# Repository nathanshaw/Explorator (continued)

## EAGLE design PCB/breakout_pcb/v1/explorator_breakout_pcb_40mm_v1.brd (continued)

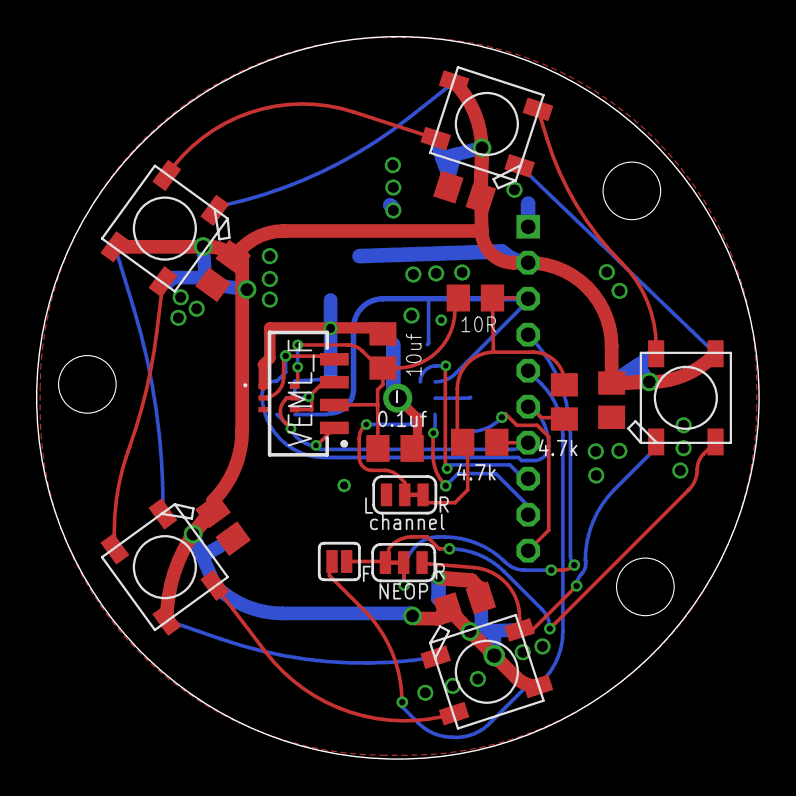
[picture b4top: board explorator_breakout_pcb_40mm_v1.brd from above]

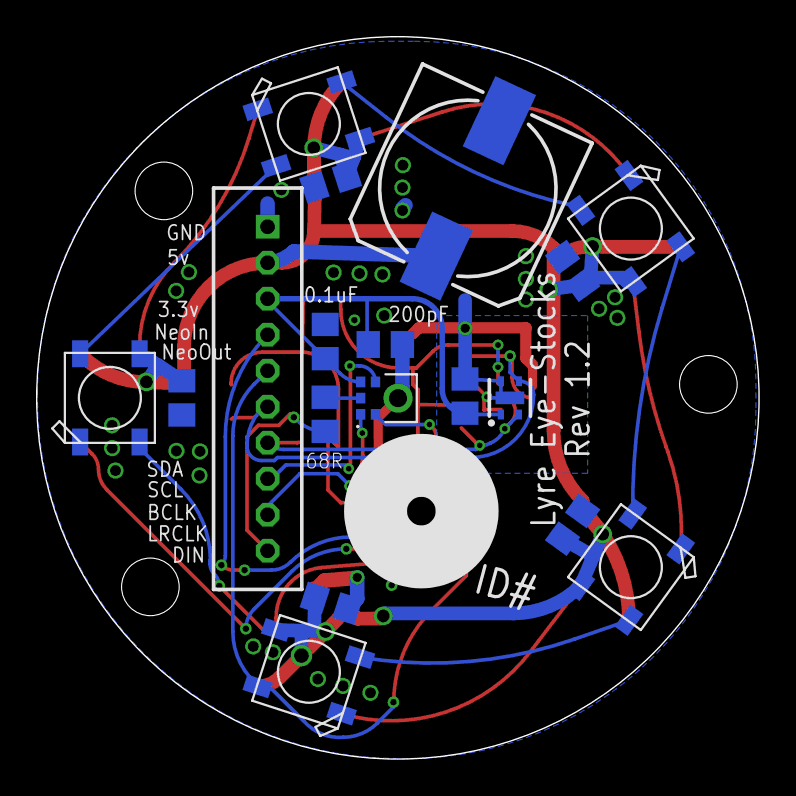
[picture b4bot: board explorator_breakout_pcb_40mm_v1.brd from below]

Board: 2 copper layers, 40.1 x 40.1 mm, 38 parts (18 on the bottom side), 23 nets.

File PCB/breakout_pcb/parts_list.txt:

Partlist

Exported from explorator_breakout_pcb_40mm_v2.sch at 3/21/23 11:15 AM

EAGLE Version 9.6.2 Copyright (c) 1988-2020 Autodesk, Inc.

Assembly variant: 

Part     Value                  Device                 Package                         Library              Sheet

C1       0.1uf                  C-USC0805              C0805                           rcl                  1
C2       0.1uF                  C-USC0805              C0805                           rcl                  1
C3       1mF                    CPOL-EU153CLV-1012     153CLV-1012                     rcl                  1
C4       10uf                   C-USC0805              C0805                           rcl                  1
C8       0.1uF                  C-USC0805              C0805                           rcl                  1
C9       200pF                  C-USC0805              C0805                           rcl                  1
JP1      JUMPER-SMT-3POS_NC_ONE JUMPER-SMT-3POS_NC_ONE SMT-JUMPER_3_1-NC_TRACE_NO-SILK nathans-custom-parts 1
JP3      JUMPER-SMT-3POS_NC_ONE JUMPER-SMT-3POS_NC_ONE SMT-JUMPER_3_1-NC_TRACE_NO-SILK nathans-custom-parts 1
JP4      JUMPER-SMT-2POS        JUMPER-SMT-2POS        SMT-JUMPER_2_NO_NO-SILK         nathans-custom-parts 1
MK_REAR  SPH-IMPROVED           SPH-IMPROVED           MIC_SPH0645LM4H-B_LARGER_RING   SPH0645LM4H-B        1
NC1      0.1uf                  C-USC0805              C0805                           rcl                  1
NC2      0.1uf                  C-USC0805              C0805                           rcl                  1
NC3      0.1uf                  C-USC0805              C0805                           rcl                  1
NC4      0.1uf                  C-USC0805              C0805                           rcl                  1
NC5      0.1uf                  C-USC0805              C0805                           rcl                  1
NC6      0.1uf                  C-USC0805              C0805                           rcl                  1
NC7      0.1uf                  C-USC0805              C0805                           rcl                  1
NC8      0.1uf                  C-USC0805              C0805                           rcl                  1
NC9      0.1uf                  C-USC0805              C0805                           rcl                  1
NC10     0.1uf                  C-USC0805              C0805                           rcl                  1
NEO_01   WS2812                 WS2812                 WS2812B                         WS2812B              1
NEO_02   WS2812                 WS2812                 WS2812B                         WS2812B              1
NEO_03   WS2812                 WS2812                 WS2812B                         WS2812B              1
NEO_04   WS2812                 WS2812                 WS2812B                         WS2812B              1
NEO_05   WS2812                 WS2812                 WS2812B                         WS2812B              1
NEO_06   WS2812                 WS2812                 WS2812B                         WS2812B              1
NEO_07   WS2812                 WS2812                 WS2812B                         WS2812B              1
NEO_08   WS2812                 WS2812                 WS2812B                         WS2812B              1
NEO_09   WS2812                 WS2812                 WS2812B                         WS2812B              1
NEO_10   WS2812                 WS2812                 WS2812B                         WS2812B              1
P1       B10B-PH-K              B10B-PH-K              B10B-PH-K                       con-jst-ph           1
R3       10R                    R-US_R0805             R0805                           PulseOximeterECG_AU  1
R5       4.7k                   R-US_R0805             R0805                           PulseOximeterECG_AU  1
R6       4.7k                   R-US_R0805             R0805                           PulseOximeterECG_AU  1
R15      68R                    R-US_R0805             R0805                           PulseOximeterECG_AU  1
U1       SHTC3                  SHTC3                  SHTC3                           SHTC3                1
U2       VEML6030-GS15          VEML6030-GS15          VISHAY_VEML6030_2X2X0.87        VEML6030-GS15        1
VEML_F   VEML7700-TT            VEML7700-TT            VEML7700                        VEML7700-TT          1

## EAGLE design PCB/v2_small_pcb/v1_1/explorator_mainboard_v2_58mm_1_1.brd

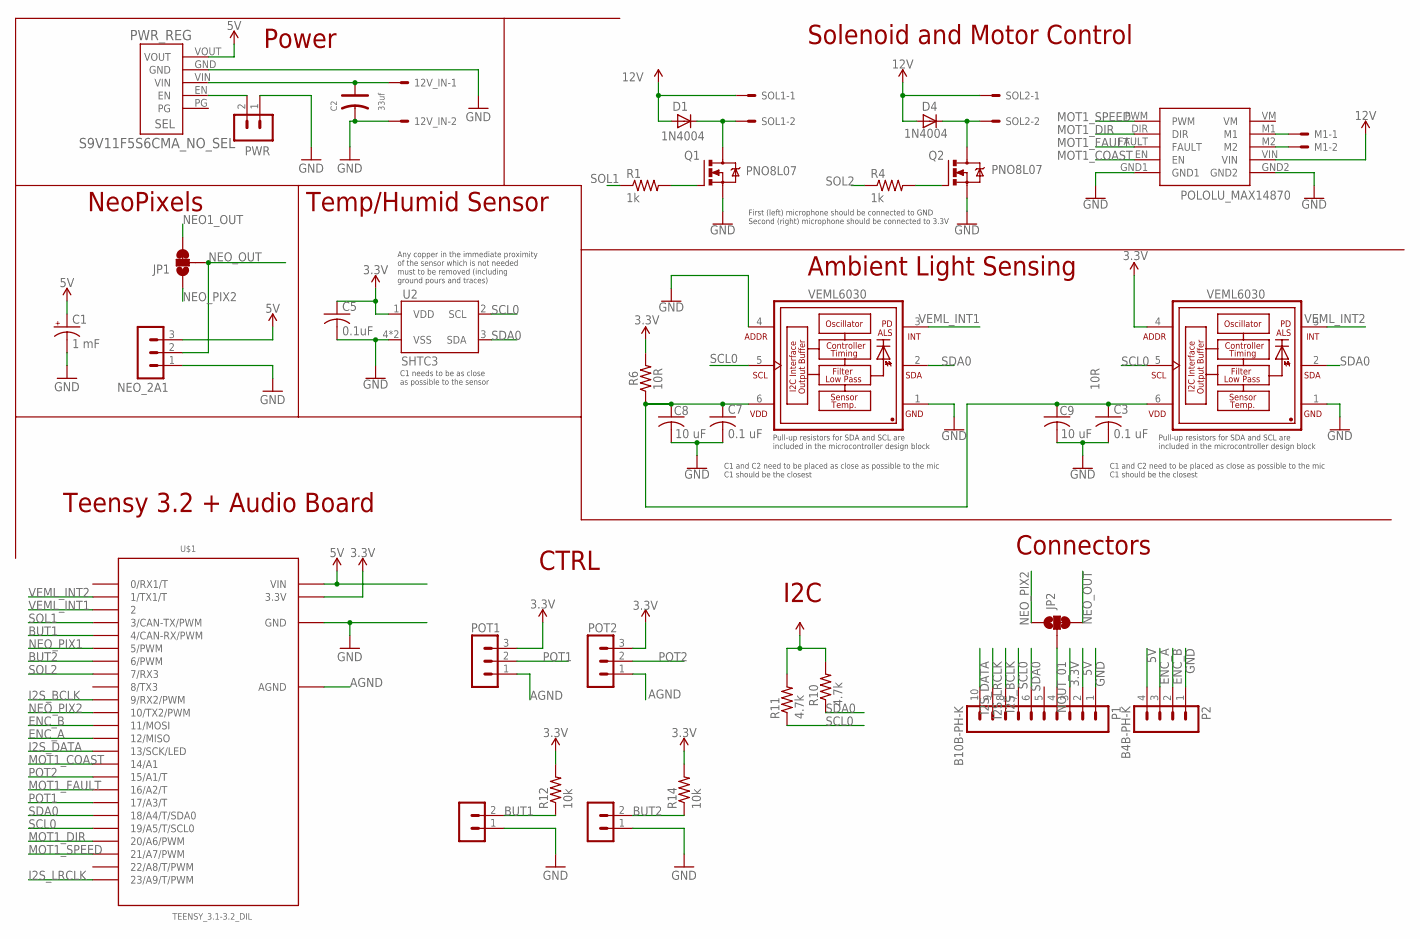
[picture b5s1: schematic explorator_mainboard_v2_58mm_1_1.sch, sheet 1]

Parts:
12V_IN: 5566-2
BUT1, BUT2: B2B-PH-K
C1: 1 mF; UD-10X10_NICHICON
C2: 33uf; PC-D5.3MM
C3, C7: 0.1 uF; C0805
C5: 0.1uF; C0805
C8, C9: 10 uF; C0805
D1, D4: 1N4004; DIODE_DO35-7
JP1, JP2: JUMPER-SMT_3_1-NC_TRACE_SILK; SMT-JUMPER_3_1-NC_TRACE_SILK
M1: 5566-2
MOT1: POLOLU_MAX14870
NEO_2A1: B3B-PH-K
P1: B10B-PH-K
P2: B4B-PH-K
POT1, POT2: B3B-PH-K
PWR: B2B-PH-K
PWR_REG: S9V11F5S6CMA_NO_SEL; S9V11F3S5CMA_NO_SEL
Q1, Q2: PNO8L07; TO220BV
R1, R4: 1k; R0805
R6: 10 R; R0805
R10, R11: 4.7k; R0805
R12, R14: 10k; R0805
SOL1, SOL2: 5566-2
U2: SHTC3
U$1: TEENSY_3.1-3.2_DIL; TEENSY_3.0-3.2&LC_DIL
VMEL1, VMEL2: VEML6030; VISHAY_VEML6030_2X2X0.87

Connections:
3.3V: C5.1, P1.3, POT1.3, POT2.3, R6.2, R10.2, R11.2, R12.2, R14.2, U2.1 (VDD), U$1.3.3V, VMEL2.4 (ADDR)
5V: C1.+, NEO_2A1.3, P1.2, P2.4, PWR_REG.VOUT, U$1.VIN; also elsewhere on the board
12V: 12V_IN.1, C2.+, D1.A (C), D4.A (C), MOT1.VIN, PWR_REG.VIN, SOL1.1, SOL2.1
AGND: POT1.1, POT2.1, U$1.AGND
BUT1: BUT1.2, R12.1, U$1.4 (4/CAN-RX/PWM)
BUT2: BUT2.2, R14.1, U$1.6 (6/PWM)
ENC_A: P2.3, U$1.12 (12/MISO)
ENC_B: P2.2, U$1.11 (11/MOSI)
GND: 12V_IN.2, BUT1.1, BUT2.1, C1.-, C2.-, C3.2, C5.2, C7.2, C8.2, C9.2, MOT1.GND1, MOT1.GND2, NEO_2A1.1, P1.1, P2.1, PWR.1, PWR_REG.GND, Q1.S, Q2.S, U2.4 (VSS), U2.5 (VSS), U$1.GND, VMEL1.1 (GND), VMEL1.4 (ADDR), VMEL2.1 (GND); also elsewhere on the board
I2S_BCLK: P1.8, U$1.9 (9/RX2/PWM)
I2S_DATA: P1.10, U$1.13 (13/SCK/LED)
I2S_LRCLK: P1.9, U$1.23/A9 (23/A9/T/PWM)
MOT1_COAST: MOT1.EN, U$1.14/A0 (14/A1)
MOT1_DIR: MOT1.DIR, U$1.20/A6 (20/A6/PWM)
MOT1_FAULT: MOT1.FAULT, U$1.16/A2 (16/A2/T)
MOT1_SPEED: MOT1.PWM, U$1.21/A7 (21/A7/PWM)
unnamed: M1.2, MOT1.M2
unnamed: M1.1, MOT1.M1
unnamed: C3.1, C7.1, C8.1, C9.1, R6.1, VMEL1.6 (VDD), VMEL2.6 (VDD)
unnamed: PWR.2, PWR_REG.EN
unnamed: Q2.G, R4.2
unnamed: D4.C (A), Q2.D, SOL2.2
unnamed: Q1.G, R1.2
unnamed: D1.C (A), Q1.D, SOL1.2
NEO1_OUT: JP1.3; also elsewhere on the board
NEO_OUT: JP1.2, JP2.3, NEO_2A1.2
NEO_PIX1: U$1.5 (5/PWM); also elsewhere on the board
NEO_PIX2: JP1.1, JP2.1, U$1.10 (10/TX2/PWM)
NOUT_01: JP2.2, P1.4
POT1: POT1.2, U$1.17/A3 (17/A3/T)
POT2: POT2.2, U$1.15/A1 (15/A1/T)
SCL0: P1.7, R11.1, U2.2 (SCL), U$1.19/A5 (19/A5/T/SCL0), VMEL1.5 (SCL), VMEL2.5 (SCL)
SDA0: P1.6, R10.1, U2.3 (SDA), U$1.18/A4 (18/A4/T/SDA0), VMEL1.2 (SDA), VMEL2.2 (SDA)
SOL1: R1.1, U$1.3 (3/CAN-TX/PWM)
SOL2: R4.1, U$1.7 (7/RX3)
VEML_INT1: U$1.2, VMEL1.3 (INT)
VEML_INT2: U$1.1 (1/TX1/T), VMEL2.3 (INT)

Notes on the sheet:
NeoPixels
I2C
Teensy 3.2 + Audio Board
Power
CTRL
10R
First (left) microphone should be connected to GND Second (right) microphone should be connected to 3.3V
C1 and C2 need to be placed as close as possible to the mic C1 should be the closest
Pull-up resistors for SDA and SCL are included in the microcontroller design block
C1 needs to be as close as possible to the sensor
Any copper in the immediate proximity of the sensor which is not needed must to be removed (including ground pours and traces)
Temp/Humid Sensor
Ambient Light Sensing
Solenoid and Motor Control
Connectors

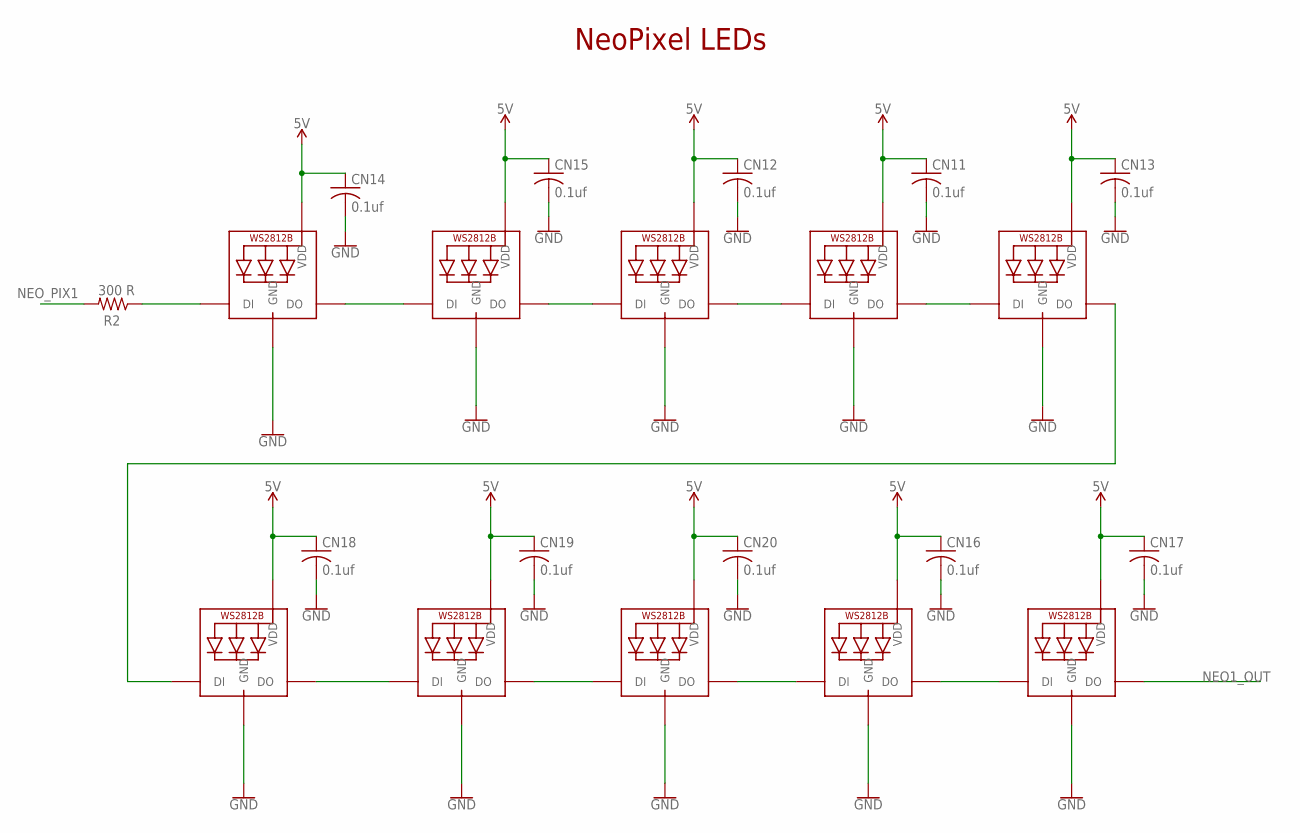
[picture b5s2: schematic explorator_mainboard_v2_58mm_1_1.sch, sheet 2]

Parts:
CN11, CN12, CN13, CN14, CN15, CN16, CN17, CN18, CN19, CN20: 0.1uf; C0805K
NEO11, NEO12, NEO13, NEO14, NEO15, NEO16, NEO17, NEO18, NEO19, NEO20: WS2812B5050; WS2812B
R2: 300 R; R0805

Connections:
5V: CN11.1, CN12.1, CN13.1, CN14.1, CN15.1, CN16.1, CN17.1, CN18.1, CN19.1, CN20.1, NEO11.1-VDD (VDD), NEO12.1-VDD (VDD), NEO13.1-VDD (VDD), NEO14.1-VDD (VDD), NEO15.1-VDD (VDD), NEO16.1-VDD (VDD), NEO17.1-VDD (VDD), NEO18.1-VDD (VDD), NEO19.1-VDD (VDD), NEO20.1-VDD (VDD); also elsewhere on the board
GND: CN11.2, CN12.2, CN13.2, CN14.2, CN15.2, CN16.2, CN17.2, CN18.2, CN19.2, CN20.2, NEO11.3-GND (GND), NEO12.3-GND (GND), NEO13.3-GND (GND), NEO14.3-GND (GND), NEO15.3-GND (GND), NEO16.3-GND (GND), NEO17.3-GND (GND), NEO18.3-GND (GND), NEO19.3-GND (GND), NEO20.3-GND (GND); also elsewhere on the board
unnamed: NEO14.2-DOUT (DO), NEO15.4-DIN (DI)
unnamed: NEO12.4-DIN (DI), NEO15.2-DOUT (DO)
unnamed: NEO11.4-DIN (DI), NEO12.2-DOUT (DO)
unnamed: NEO11.2-DOUT (DO), NEO13.4-DIN (DI)
unnamed: NEO13.2-DOUT (DO), NEO18.4-DIN (DI)
unnamed: NEO14.4-DIN (DI), R2.1
unnamed: NEO18.2-DOUT (DO), NEO19.4-DIN (DI)
unnamed: NEO19.2-DOUT (DO), NEO20.4-DIN (DI)
unnamed: NEO16.4-DIN (DI), NEO20.2-DOUT (DO)
unnamed: NEO16.2-DOUT (DO), NEO17.4-DIN (DI)
NEO1_OUT: NEO17.2-DOUT (DO); also elsewhere on the board
NEO_PIX1: R2.2; also elsewhere on the board

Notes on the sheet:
NeoPixel LEDs

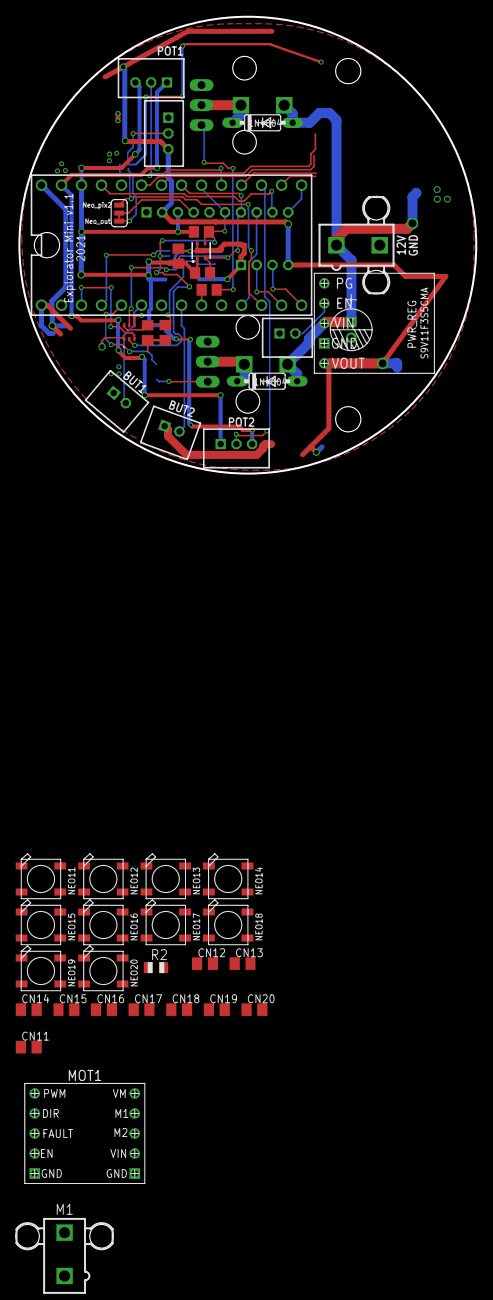
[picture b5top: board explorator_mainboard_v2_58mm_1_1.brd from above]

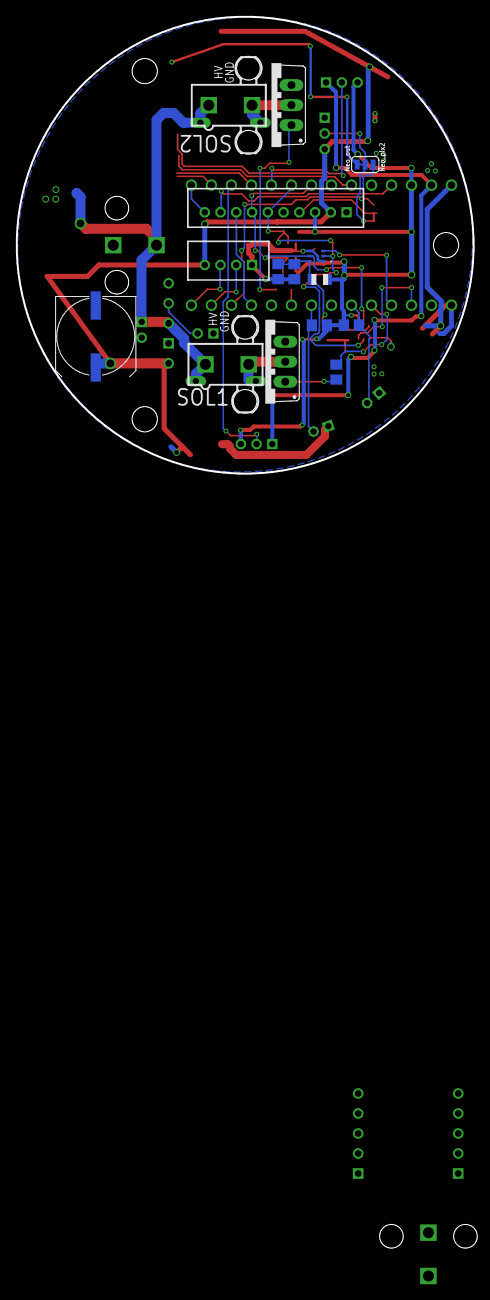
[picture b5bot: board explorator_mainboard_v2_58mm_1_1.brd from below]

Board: 2 copper layers, 58.0 x 58.0 mm, 59 parts (15 on the bottom side), 47 nets.

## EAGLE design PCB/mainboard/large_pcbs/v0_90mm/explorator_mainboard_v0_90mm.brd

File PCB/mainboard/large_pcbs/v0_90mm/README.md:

## Explorator Mainboard v0 (Prototype) 90mm

## Schematic

## Layout
| Bottom  |  Both  |  Top  |
| ------- | ------- | ------- |
|  |  |  |

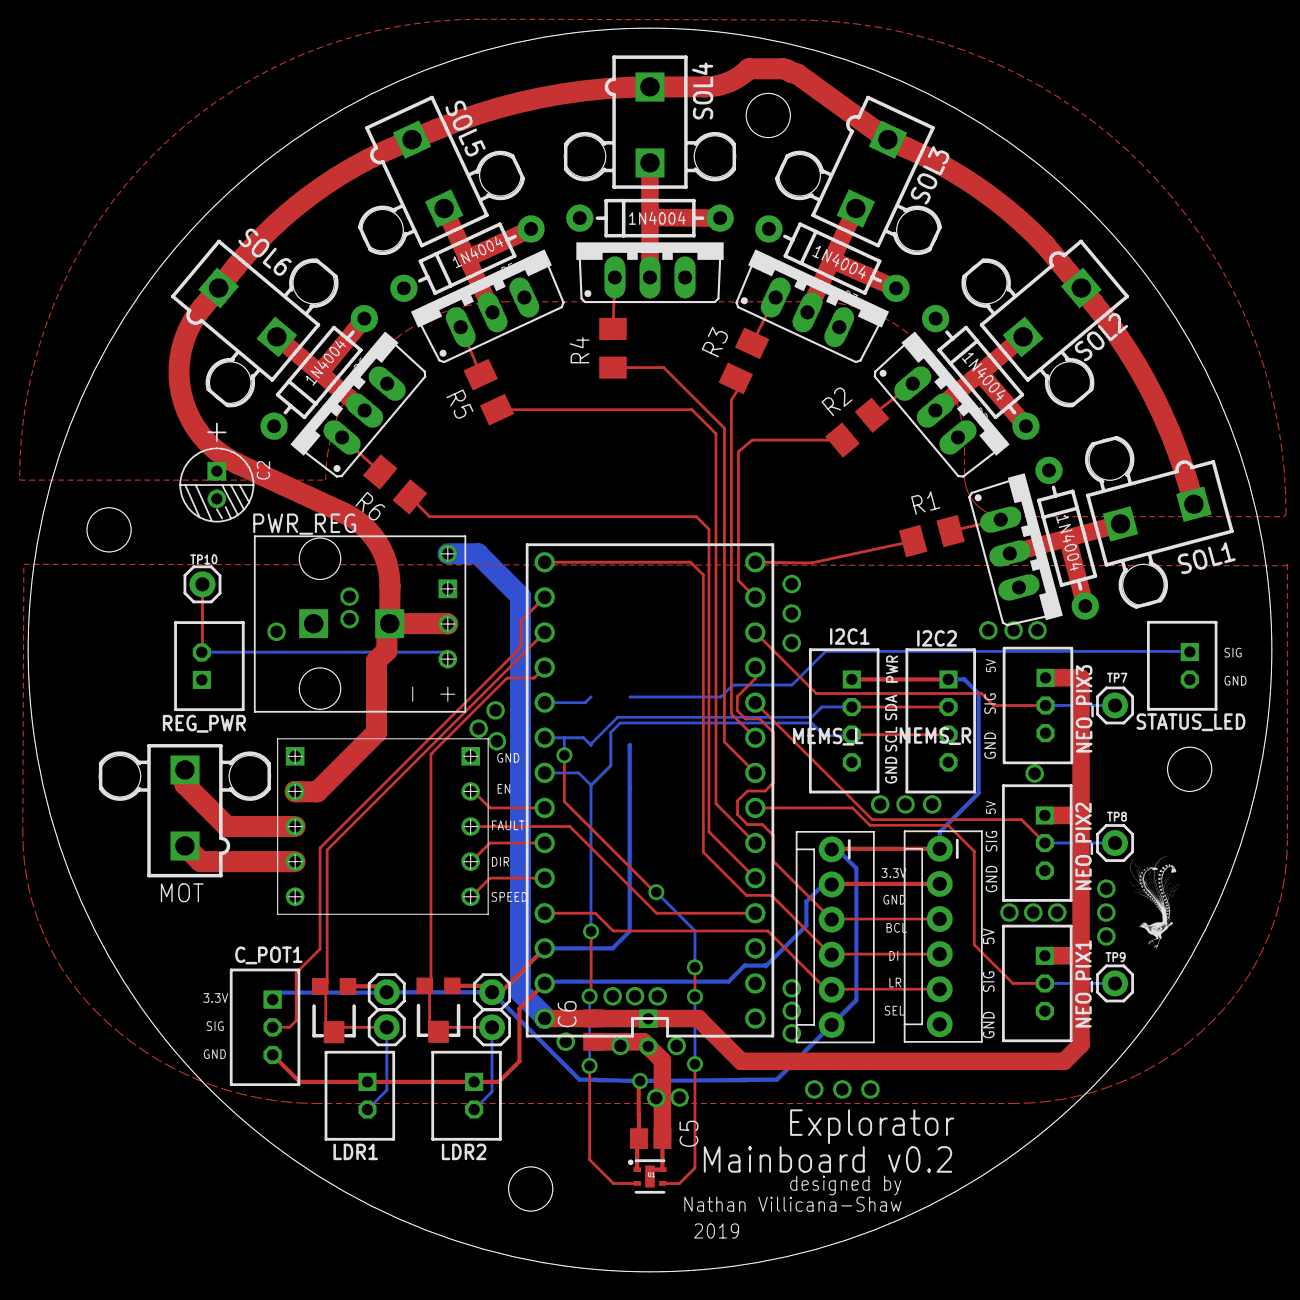
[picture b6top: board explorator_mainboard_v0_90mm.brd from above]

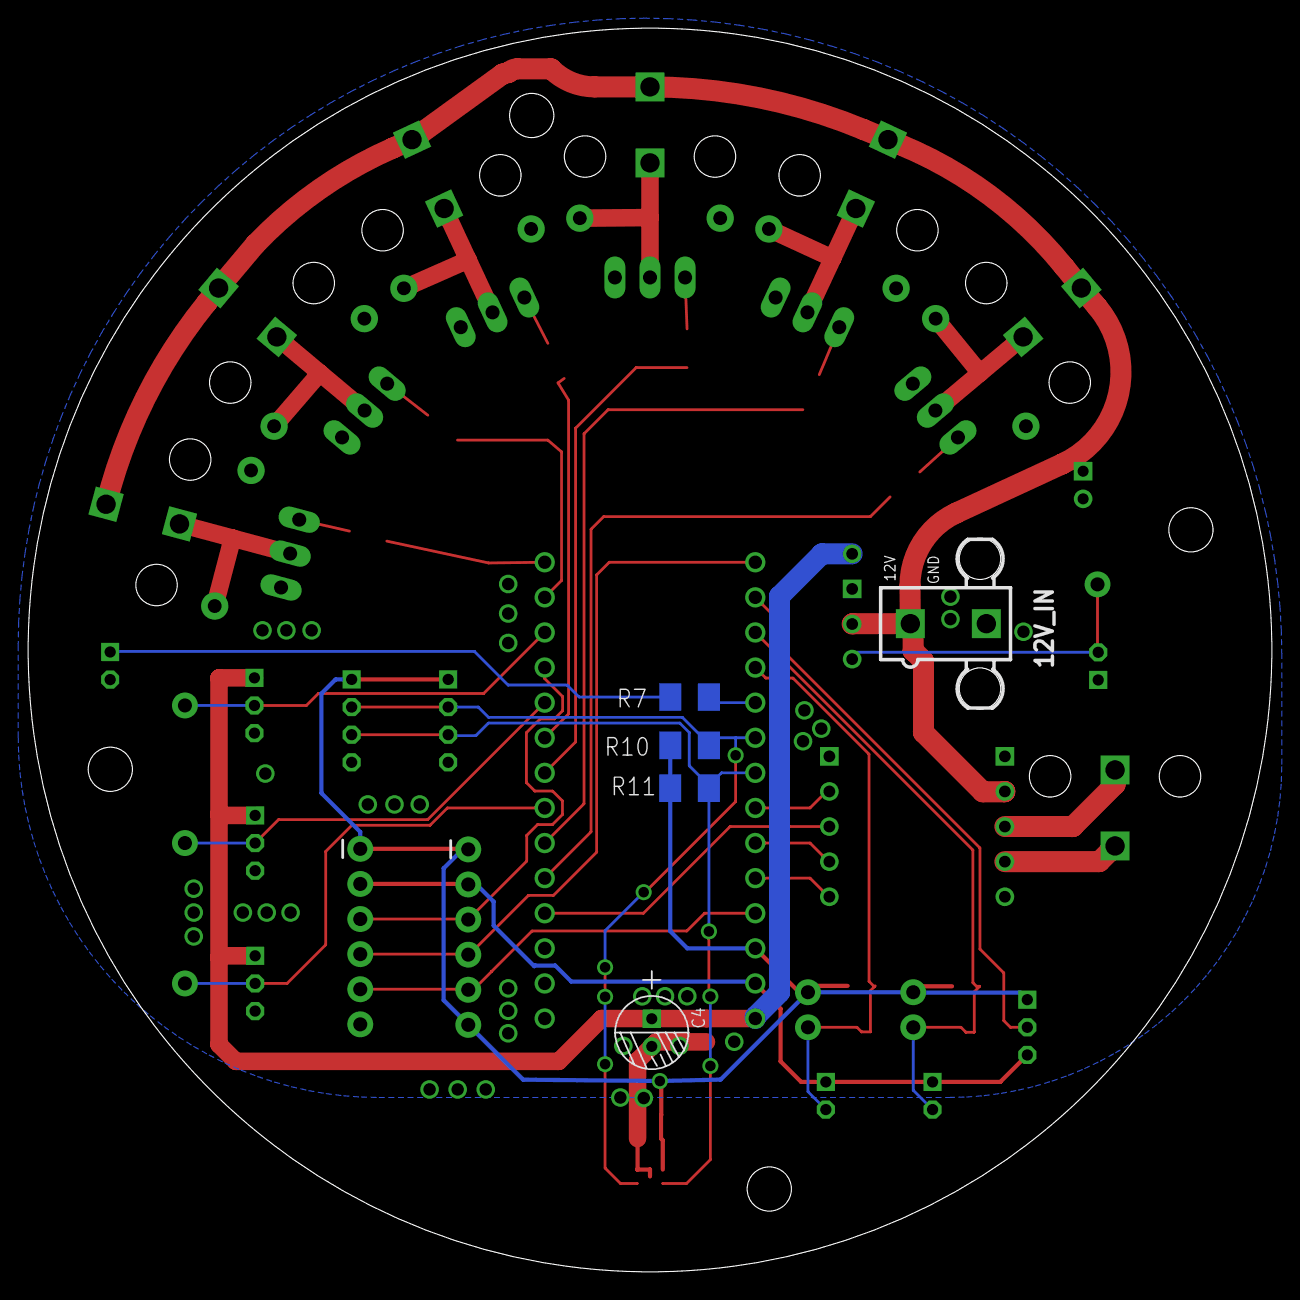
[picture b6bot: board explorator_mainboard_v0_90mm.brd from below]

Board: 2 copper layers, 90.0 x 90.0 mm, 59 parts (5 on the bottom side), 43 nets.

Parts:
12V_IN: 5566-2
C2: 33uf; PC-D5.3MM
C4: 10uf; PC-D5.3MM
C5, C6: 100nf; C2012
C_POT1: B3B-PH-K
D1, D2, D3, D4, D5, D6: 1N4004; DIODE-1N4001
I2C1, I2C2: B4B-PH-K
LDR1, LDR2: B2B-PH-K
MEMS_L: MOLEX-1X6
MEMS_R: MOLEX-1X6
MOT: 5566-2
NEO_PIX1, NEO_PIX2, NEO_PIX3: B3B-PH-K
PWR_REG: S9V11F5S6CMA_MISSINIG_PINS; S9V11F3S5CMA_MISSING_PINS
Q1, Q2, Q3, Q4, Q5, Q6: PNO8L07; TO220BV
R1, R2, R3, R4, R5, R6: 1k; M1206
R7: 220R; M1206
R10, R11: 4.7k; M1206
REG_PWR: B2B-PH-K
SOL1, SOL2, SOL3, SOL4, SOL5, SOL6: 5566-2
STATUS_LED: B2B-PH-K
TM1, TM2: 100k; TC33X
TP3: ldr1_test_h; 1X01
TP4: ldr2_test_h; 1X01
TP5: ldr2_test_l; 1X01
TP6: ldr1_test_l; 1X01
TP7: neop_test3; 1X01
TP8: neop_test2; 1X01
TP9: neop_test1; 1X01
TP10: en_test; 1X01
U1: SHTC3
U$1: POLOLU_MAX14870
U$3: TEENSY_3.1-3.2_DIL; TEENSY_3.0-3.2&LC_DIL

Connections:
3.3V: C5.1, C_POT1.1, I2C1.1, I2C2.1, MEMS_L.1, MEMS_L.6, MEMS_R.1, R10.2, R11.2, TM1.1, TM2.1, TP3.1, TP4.1, U1.1, U$3.3.3V
5V: C4.+, C6.1, NEO_PIX1.1, NEO_PIX2.1, NEO_PIX3.1, PWR_REG.VOUT, U$3.VIN
12V: 12V_IN.1, C2.+, D1.C, D2.C, D3.C, D4.C, D5.C, D6.C, PWR_REG.VIN, SOL1.1, SOL2.1, SOL3.1, SOL4.1, SOL5.1, SOL6.1, U$1.VIN
AGND: C_POT1.3, LDR1.1, LDR2.1, MEMS_L.2, MEMS_R.2, U$3.AGND
GND: 12V_IN.2, C2.-, C4.-, C5.2, C6.2, I2C1.4, I2C2.4, MEMS_R.6, NEO_PIX1.3, NEO_PIX2.3, NEO_PIX3.3, PWR_REG.GND, Q1.S, Q2.S, Q3.S, Q4.S, Q5.S, Q6.S, REG_PWR.1, STATUS_LED.2, U1.4, U1.5, U$1.GND1, U$1.GND2, U$3.GND
I2S_BCLK: MEMS_L.3, MEMS_R.3, U$3.9
I2S_DATA: MEMS_L.4, MEMS_R.4, U$3.13
I2S_LRCLK: MEMS_L.5, MEMS_R.5, U$3.23/A9
LDR1: LDR1.2, TM1.2, TM1.3, TP6.1, U$3.15/A1
LDR2: LDR2.2, TM2.2, TM2.3, TP5.1, U$3.16/A2
LED: R7.1, U$3.17/A3
MOT_COAST: U$1.EN, U$3.20/A6
MOT_DIR: U$1.DIR, U$3.21/A7
MOT_FAULT: U$1.FAULT, U$3.2
MOT_SPEED: U$1.PWM, U$3.22/A8
unnamed: Q5.G, R5.2
unnamed: D5.A, Q5.D, SOL5.2
unnamed: Q6.G, R6.2
unnamed: Q2.G, R2.2
unnamed: D6.A, Q6.D, SOL6.2
unnamed: R7.2, STATUS_LED.1
unnamed: D2.A, Q2.D, SOL2.2
unnamed: PWR_REG.EN, REG_PWR.2, TP10.1
unnamed: Q3.G, R3.2
unnamed: D3.A, Q3.D, SOL3.2
unnamed: Q4.G, R4.2
unnamed: D4.A, Q4.D, SOL4.2
unnamed: Q1.G, R1.2
unnamed: D1.A, Q1.D, SOL1.2
unnamed: MOT.2, U$1.M2
unnamed: MOT.1, U$1.M1
NEO_PIX1: NEO_PIX1.2, TP9.1, U$3.5
NEO_PIX2: NEO_PIX2.2, TP8.1, U$3.8
NEO_PIX3: NEO_PIX3.2, TP7.1, U$3.10
POT1: C_POT1.2, U$3.14/A0
SCL0: I2C1.3, I2C2.3, R11.1, U1.2, U$3.19/A5
SDA0: I2C1.2, I2C2.2, R10.1, U1.3, U$3.18/A4
SOL1: R1.1, U$3.12
SOL2: R2.1, U$3.11
SOL3: R3.1, U$3.7
SOL4: R4.1, U$3.6
SOL5: R5.1, U$3.4
SOL6: R6.1, U$3.3

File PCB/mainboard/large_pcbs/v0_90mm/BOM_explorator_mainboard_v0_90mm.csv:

"Qty";"Value";"Device";"Package";"Parts";"Description";"LABEL";"MF";"MPN";"OC_FARNELL";"OC_NEWARK";"VALUE";
"4";"";"B3B-PH-K";"B3B-PH-K";"C_POT1, NEO_PIX1, NEO_PIX2, NEO_PIX3";"HEADER";"";"";"";"";"";"";
"2";"";"CONN_06POLAR";"MOLEX-1X6";"MEMS_L, MEMS_R";"Multi connection point. Often used as Generic Header-pin footprint for 0.1 inch spaced/style header connections";"";"";"";"";"";"";
"2";"100k";"TRIMPOTTC33X";"TC33X";"TM1, TM2";"SMT trimmer potentiometer part number TC33X";"";"";"";"";"";"";
"2";"100nf";"C-USC2012";"C2012";"C5, C6";"CAPACITOR, American symbol";"";"";"";"";"";"";
"1";"10uf";"DIP-ALUMINUM-47UF-16V(D5-H7MM)";"PC-D5.3MM";"C4";"302030033";"";"";"KS 100uF/16V";"";"";"100uf";
"6";"1N4004";"DIODEPTH";"DIODE-1N4001";"D1, D2, D3, D4, D5, D6";"Diode";"";"";"";"";"";"";
"6";"1k";"R-US_M1206";"M1206";"R1, R2, R3, R4, R5, R6";"RESISTOR, American symbol";"";"";"";"";"";"";
"1";"220R";"R-US_M1206";"M1206";"R7";"RESISTOR, American symbol";"";"";"";"";"";"";
"1";"33uf";"DIP-ALUMINUM-47UF-16V(D5-H7MM)";"PC-D5.3MM";"C2";"302030033";"";"";"KS 100uF/16V";"";"";"100uf";
"2";"4.7k";"R-US_M1206";"M1206";"R10, R11";"RESISTOR, American symbol";"";"";"";"";"";"";
"8";"5566-2";"5566-2";"5566-2";"12V_IN, MOT, SOL1, SOL2, SOL3, SOL4, SOL5, SOL6";"Mini FIT connector 2 pol";"";"MOLEX";"";"1822072";"unknown";"";
"4";"B2B-PH-K";"B2B-PH-K";"B2B-PH-K";"LDR1, LDR2, REG_PWR, STATUS_LED";"HEADER";"";"";"";"";"";"";
"2";"B4B-PH-K";"B4B-PH-K";"B4B-PH-K";"I2C1, I2C2";"HEADER";"";"";"";"";"";"";
"6";"PNO8L07";"IRF540";"TO220BV";"Q1, Q2, Q3, Q4, Q5, Q6";"HEXFET Power MOSFET";"";"";"";"";"";"";
"1";"POLOLU_MAX14870";"POLOLU_MAX14870";"POLOLU_MAX14870";"U$1";"";"";"";"";"";"";"";
"1";"S9V11F5S6CMA_MISSINIG_PINS";"S9V11F5S6CMA_MISSINIG_PINS";"S9V11F3S5CMA_MISSING_PINS";"PWR_REG";"";"";"";"";"";"";"";
"1";"SHTC3";"SHTC3";"SHTC3";"U1";"";"";"";"";"";"";"";
"1";"TEENSY_3.1-3.2_DIL";"TEENSY_3.1-3.2_DIL";"TEENSY_3.0-3.2&LC_DIL";"U$3";"Teensy 3.1 or 3.2 in a DIL Layout.";"";"";"";"";"";"";
"1";"en_test";"CONN_01";"1X01";"TP10";"Single connection point. Often used as Generic Header-pin footprint for 0.1 inch spaced/style header connections";"";"";"";"";"";"";
"1";"ldr1_test_h";"CONN_01";"1X01";"TP3";"Single connection point. Often used as Generic Header-pin footprint for 0.1 inch spaced/style header connections";"";"";"";"";"";"";
"1";"ldr1_test_l";"CONN_01";"1X01";"TP6";"Single connection point. Often used as Generic Header-pin footprint for 0.1 inch spaced/style header connections";"";"";"";"";"";"";
"1";"ldr2_test_h";"CONN_01";"1X01";"TP4";"Single connection point. Often used as Generic Header-pin footprint for 0.1 inch spaced/style header connections";"";"";"";"";"";"";
"1";"ldr2_test_l";"CONN_01";"1X01";"TP5";"Single connection point. Often used as Generic Header-pin footprint for 0.1 inch spaced/style header connections";"";"";"";"";"";"";
"1";"neop_test1";"CONN_01";"1X01";"TP9";"Single connection point. Often used as Generic Header-pin footprint for 0.1 inch spaced/style header connections";"";"";"";"";"";"";
"1";"neop_test2";"CONN_01";"1X01";"TP8";"Single connection point. Often used as Generic Header-pin footprint for 0.1 inch spaced/style header connections";"";"";"";"";"";"";
"1";"neop_test3";"CONN_01";"1X01";"TP7";"Single connection point. Often used as Generic Header-pin footprint for 0.1 inch spaced/style header connections";"";"";"";"";"";"";
